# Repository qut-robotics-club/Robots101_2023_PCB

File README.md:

# ROBOTS101_2023

Goal:
To create a easy funtional Pi hat for the ROBOTS101 program.

This pi hat will:
- Label all pins & connections clearly.
- Have breakout headers to reduce confusion and reduce dangerous connections
- Regulate battery voltage & power the Pi safely 
- Provide a direct and clear power switch
- (Optional) Expand GPIO for future projects 
- Clean and streamline robot construction.
- Have an easy design for future PCB workshop to work on

ROBOTS101 WIKI LINK: https://goofy-slicer-49c.notion.site/ROBOTS101-Wiki-223888f84ce34d78a62f8b15874e6fb9

## Key Features
1. Battery Connector
    - XT30 PCB Mount
2. Power Regulation 
    - 5.1V Regulation
        - Limit to 2.5A
        - Needs filtering capacitors
        - Regulators can be bought from store
    - 3.3V Regulation? (unsure if necessary)
3. Reverse Polarity 
    - P-MOSFET
4. User Feedback
    - Buttons
    - LEDS
5. Expansion 
    - I2C address lanes - breakout into multiple connectors
6. Breakouts
    - Motor control board
    - Single Gripper Servo or two??
    - Ultrasonic Sensor
    - Adafruit Mini PiTFT support

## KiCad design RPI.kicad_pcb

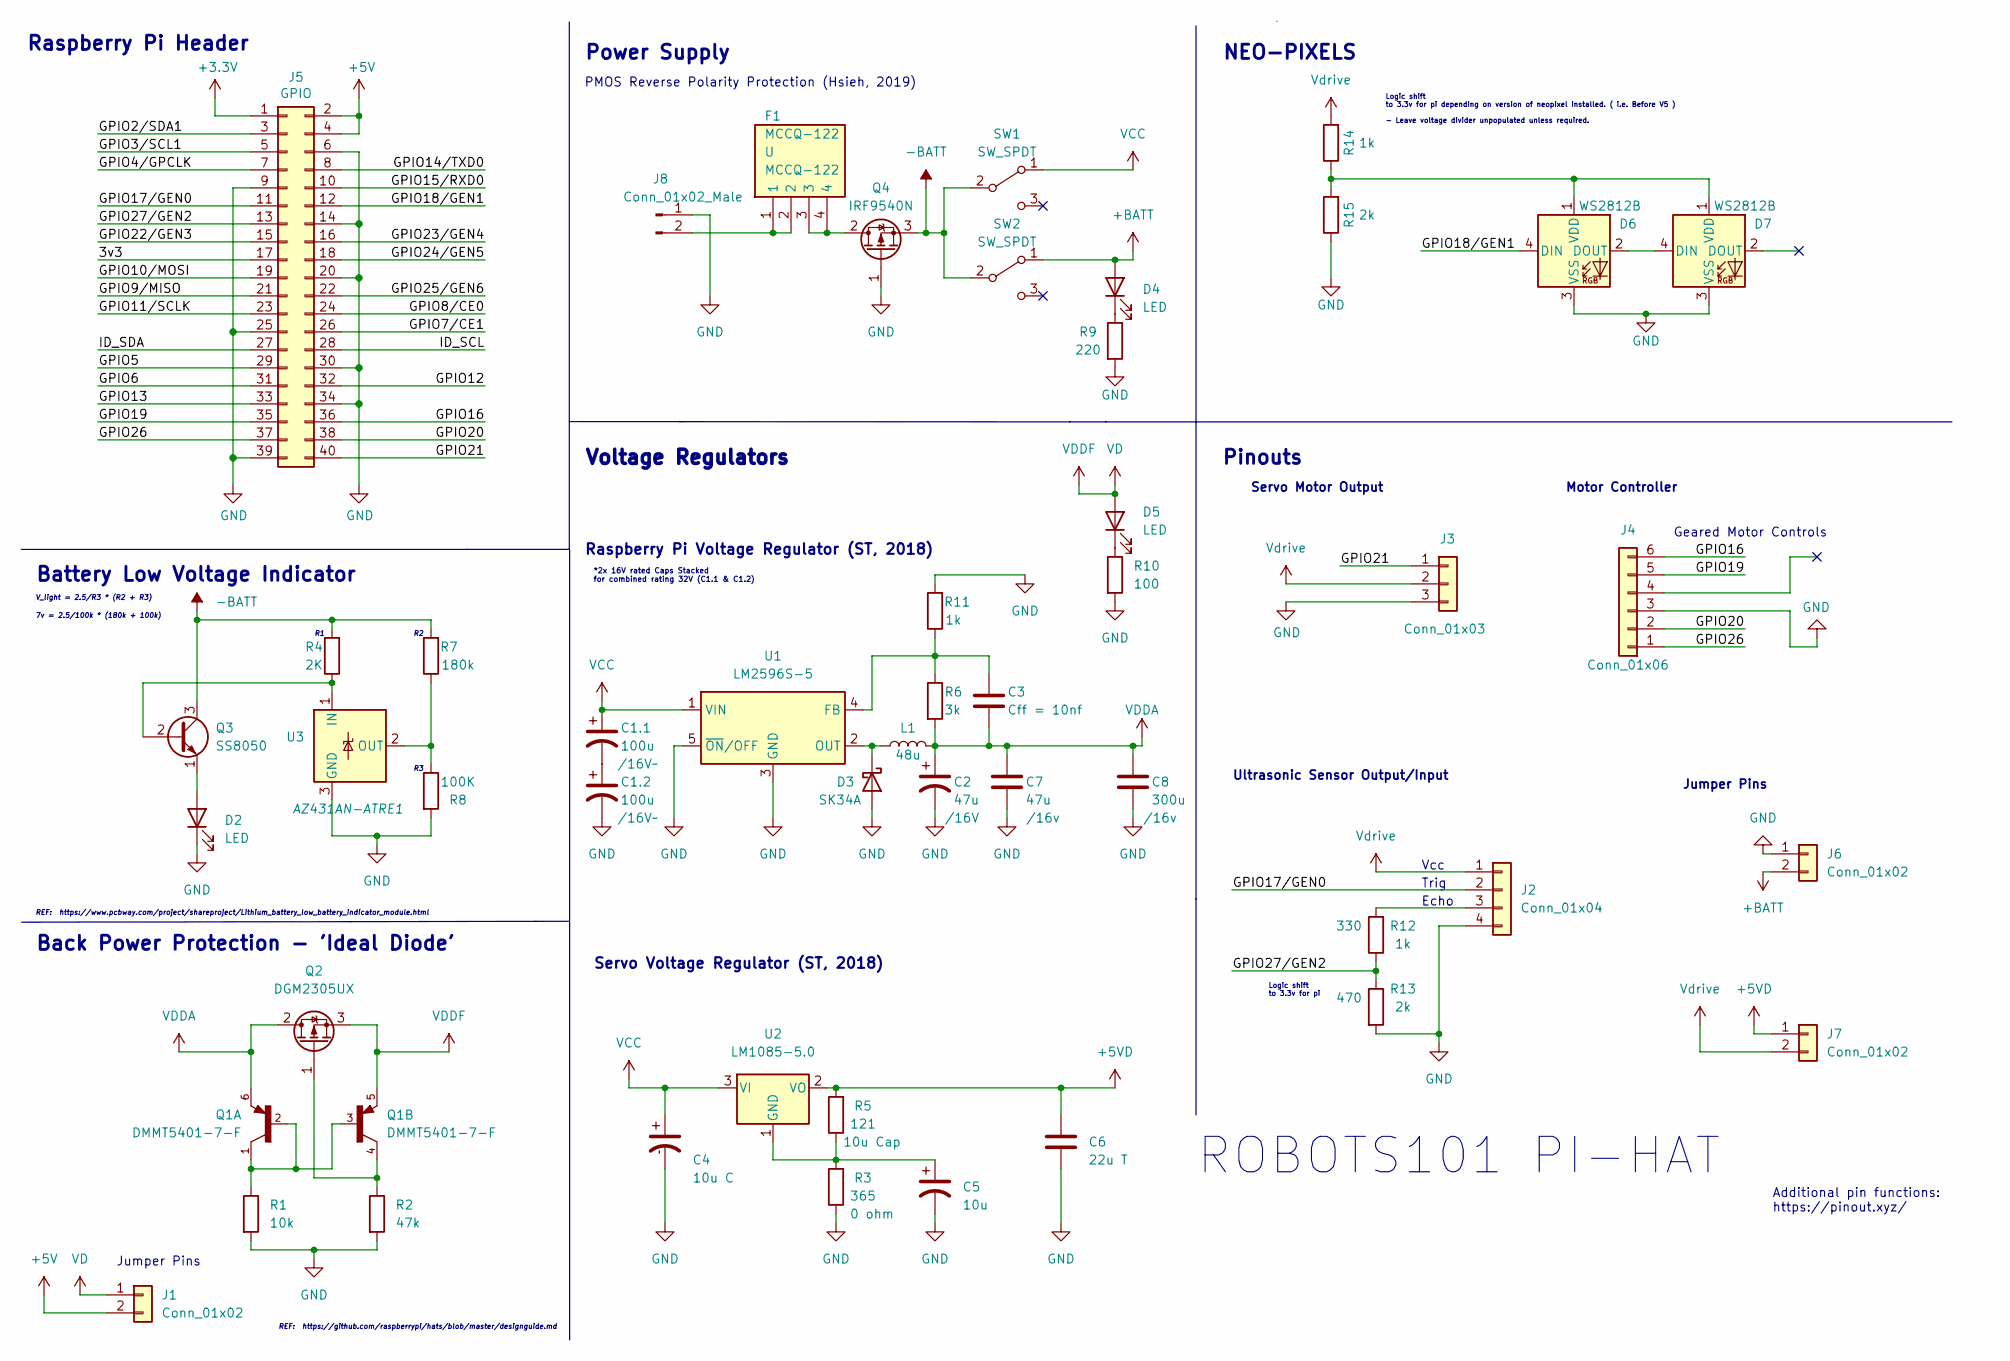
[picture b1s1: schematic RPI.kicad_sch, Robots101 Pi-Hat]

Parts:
C1.1, C1.2: 100u; C_1210_3225Metric_Pad1.33x2.70mm_HandSolder; Voltage /16V~
C2: 47u; C_0805_2012Metric_Pad1.18x1.45mm_HandSolder; Voltage /16V
C3: Cff = 10nf; C_0805_2012Metric_Pad1.18x1.45mm_HandSolder
C4: 10u C; C_0805_2012Metric_Pad1.18x1.45mm_HandSolder
C5: 10u; C_0805_2012Metric_Pad1.18x1.45mm_HandSolder
C6: 22u T; C_0805_2012Metric_Pad1.18x1.45mm_HandSolder
C7: 47u; C_0805_2012Metric_Pad1.18x1.45mm_HandSolder; Voltage /16v
C8: 300u; CP_Radial_D5.0mm_P2.50mm; Voltage /16v
D2, D4, D5: LED; D_0805_2012Metric_Pad1.15x1.40mm_HandSolder
D3: SK34A; D_SMA_Handsoldering
D6, D7: WS2812B; LED_WS2812B_PLCC4_5.0x5.0mm_P3.2mm
F1: MCCQ-122; MCCQ122; Manufacturer_Part_Number MCCQ-122
J1, J7: Conn_01x02; PinSocket_1x02_P2.54mm_Vertical
J2: Conn_01x04; PinSocket_1x04_P2.54mm_Vertical
J3: Conn_01x03; PinSocket_1x03_P2.54mm_Vertical
J4: Conn_01x06; PinSocket_1x06_P2.54mm_Vertical
J5: GPIO; PinSocket_2x20_P2.54mm_Vertical
J6: Conn_01x02; TE_282836-2
J8: Conn_01x02_Male; AMASS_XT30PW-M_1x02_P2.50mm_Horizontal
L1: 48u; L_Bourns_SRR1260
Q1: DMMT5401-7-F; SOT-23-6_Handsoldering; PARTREV 8
Q2: DGM2305UX; SOT-23
Q3: SS8050; SOT-23-3
Q4: IRF9540N; TO-220-3_Vertical
R1: 10k; R_0805_2012Metric_Pad1.20x1.40mm_HandSolder
R2: 47k; R_0805_2012Metric_Pad1.20x1.40mm_HandSolder
R3: 365; R_0805_2012Metric_Pad1.20x1.40mm_HandSolder
R4: 2K; R_0805_2012Metric_Pad1.20x1.40mm_HandSolder
R5: 121; R_0805_2012Metric_Pad1.20x1.40mm_HandSolder
R6: 3k; R_0805_2012Metric_Pad1.20x1.40mm_HandSolder
R7: 180k; R_0805_2012Metric_Pad1.20x1.40mm_HandSolder
R8: 100K; R_0805_2012Metric_Pad1.20x1.40mm_HandSolder
R9: 220; R_0805_2012Metric_Pad1.20x1.40mm_HandSolder
R10: 100; R_0805_2012Metric_Pad1.20x1.40mm_HandSolder
R11, R12, R14: 1k; R_0805_2012Metric_Pad1.20x1.40mm_HandSolder
R13, R15: 2k; R_0805_2012Metric_Pad1.20x1.40mm_HandSolder
SW1, SW2: SW_SPDT; Switch_SPDT_Jaycar
U1: LM2596S-5; TO-263-5_TabPin3
U2: LM1085-5.0; TO-220-3_Vertical
U3: AZ431AN-ATRE1; SOT-23-3

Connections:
+3V3: J5.1
+5V: J1.2, J5.2, J5.4
+5VD: C6.1, J7.1, R5.2, U2.2 (VO)
+BATT: D4.2 (A), J6.2, SW2.1 (A)
-BATT: Q3.3 (C), Q4.3 (S), R4.2, R7.2, SW1.2 (B), SW2.2 (B)
/3v3: J5.17
/GPIO2/SDA1: J5.3
/GPIO3/SCL1: J5.5
/GPIO4/GPCLK: J5.7
/GPIO5: J5.29
/GPIO6: J5.31
/GPIO7/CE1: J5.26
/GPIO8/CE0: J5.24
/GPIO9/MISO: J5.21
/GPIO10/MOSI: J5.19
/GPIO11/SCLK: J5.23
/GPIO12: J5.32
/GPIO13: J5.33
/GPIO14/TXD0: J5.8
/GPIO15/RXD0: J5.10
/GPIO16: J4.6, J5.36
/GPIO17/GEN0: J2.2, J5.11
/GPIO18/GEN1: D6.4 (DIN), J5.12
/GPIO19: J4.5, J5.35
/GPIO20: J4.2, J5.38
/GPIO21: J3.1, J5.40
/GPIO22/GEN3: J5.15
/GPIO23/GEN4: J5.16
/GPIO24/GEN5: J5.18
/GPIO25/GEN6: J5.22
/GPIO26: J4.1, J5.37
/GPIO27/GEN2: J5.13, R12.1, R13.1
/ID_SCL: J5.28
/ID_SDA: J5.27
GND: C1.2.2, C2.2, C4.2, C5.2, C6.2, C7.2, C8.2, D2.1 (K), D3.2 (A), D6.3 (VSS), D7.3 (VSS), J2.4, J3.3, J4.3, J5.6, J5.9, J5.14, J5.20, J5.25, J5.30, J5.34, J5.39, J6.1, J8.1, Q4.1 (G), R1.2, R2.2, R3.1, R8.2, R9.2, R10.2, R11.2, R13.2, R15.1, U1.3 (GND), U1.5 (~ON/OFF), U3.3 (GND)
unnamed: C1.1.2, C1.2.1
unnamed: C3.1, R6.1, R11.1, U1.4 (FB)
unnamed: C5.1, R3.2, R5.1, U2.1 (GND)
unnamed: D2.2 (A), Q3.1 (E)
unnamed: D3.1 (K), L1.1, U1.2 (OUT)
unnamed: D4.1 (K), R9.1
unnamed: D5.1 (K), R10.1
unnamed: D6.1 (VDD), D7.1 (VDD), R14.1, R15.2
unnamed: D6.2 (DOUT), D7.4 (DIN)
unnamed: F1.1, F1.2, J8.2
unnamed: F1.3, F1.4, Q4.2 (D)
unnamed: J2.3, R12.2
unnamed: Q1.1, Q1.2, Q1.3, R1.1
unnamed: Q1.4, Q2.1 (G), R2.1
unnamed: Q3.2 (B), R4.1, U3.1 (IN)
unnamed: R7.1, R8.1, U3.2 (OUT)
VCC: C1.1.1, C4.1, SW1.1 (A), U1.1 (VIN), U2.3 (VI)
VD: D5.2 (A), J1.1, Q1.5, Q2.3 (S)
VDDA: C2.1, C3.2, C7.1, C8.1, L1.2, Q1.6, Q2.2 (D), R6.2
Vdrive: J2.1, J3.2, J7.2, R14.2

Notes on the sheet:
REF: https://github.com/raspberrypi/hats/blob/master/designguide.md
ROBOTS101 PI-HAT
Logic shift to 3.3v for pi
Battery Low Voltage Indicator
Raspberry Pi Header
Vcc
Jumper Pins
Pinouts
Additional pin functions: https://pinout.xyz/
Servo Motor Output
REF: https://www.pcbway.com/project/shareproject/Lithium_battery_low_battery_indicator_module.html
PMOS Reverse Polarity Protection (Hsieh, 2019)
V_light = 2.5/R3 * (R2 + R3)
*2x 16V rated Caps Stacked for combined rating 32V (C1.1 & C1.2)
Servo Voltage Regulator (ST, 2018)
Echo
Power Supply
Logic shift to 3.3v for pi depending on version of neopixel installed. ( i.e. Before V5 ) - Leave voltage divider unpopulated unless required.
Trig
Ultrasonic Sensor Output/Input
Back Power Protection - 'Ideal Diode'
Motor Controller
7v = 2.5/100k * (180k + 100k)
Raspberry Pi Voltage Regulator (ST, 2018)
Voltage Regulators
NEO-PIXELS
Geared Motor Controls

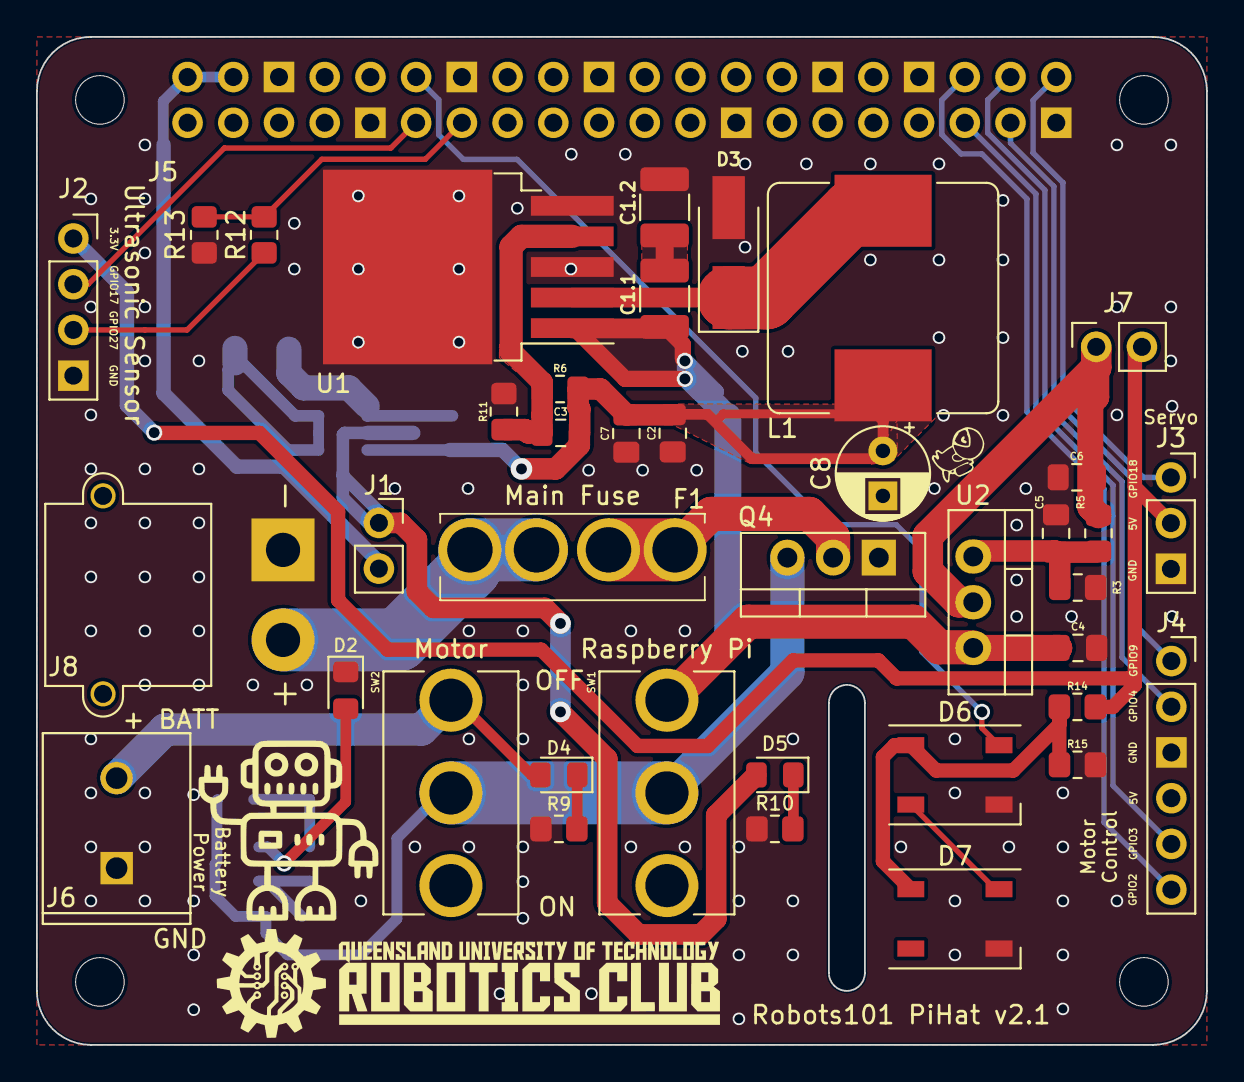
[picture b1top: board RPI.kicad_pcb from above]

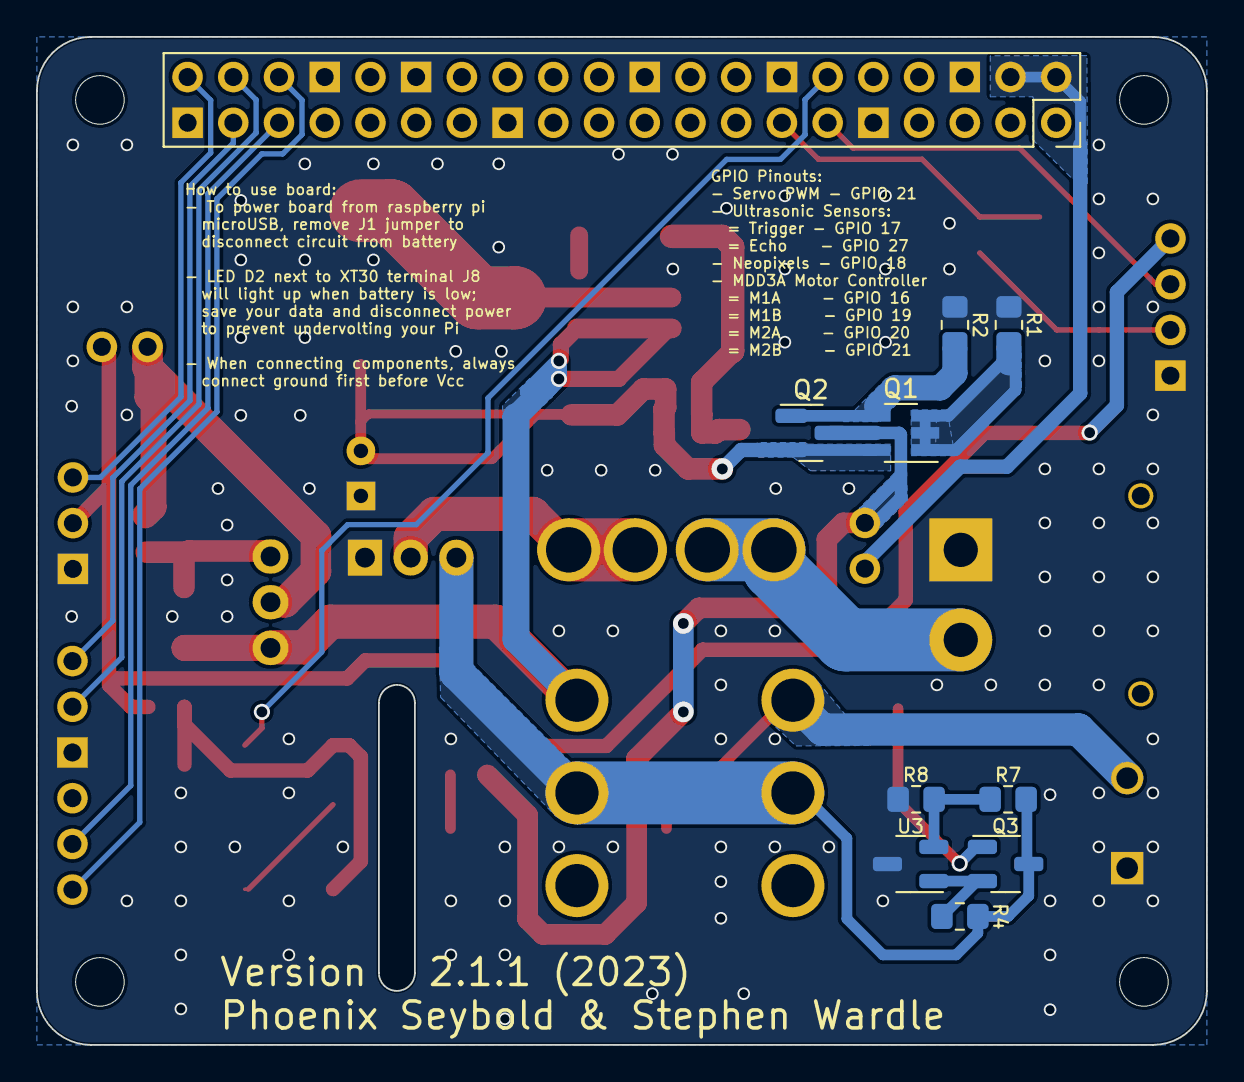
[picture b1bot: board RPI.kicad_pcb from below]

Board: 2 copper layers, 65.0 x 56.0 mm, 56 parts (10 on the bottom side), 33 nets.

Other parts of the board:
G: LOGO
G#2: LOGO
MH1, MH2, MH3, MH4: MountingHole_2.7mm_M2.5
ROBOTS101: LOGO

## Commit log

2023-02-13 adding stevens 1st PCB draft
2023-02-13 added folder structure | UNFORTUNATLY REQUIRED DUMMY TEXT FILES
2023-02-13 Update README.md
    feature overview
2023-02-16 Updated MOSFET and Vreg to be store-accessible
2023-02-16 Spelling error correction and updates of README.md
2023-02-16 Updated Adafruit Pinouts & Pi Pinouts
2023-02-17 Adding part numbers + updated footprint for a pin
2023-03-01 Updated GPIO numbers correctly on pi
2023-03-02 Updates made to reflect actual correct pin labels
2023-03-02 Updated for motor driver, UV sensor, & servo pins
2023-03-02 Schematic Completed
2023-03-03 Added diode protection and switches
2023-03-03 Revisions made?
2023-03-03 Small update
2023-03-05 Removed EEPROM, Added back power protection
2023-03-15 Process to update headers for SMDs
2023-03-15 Component footprints done - only need cap & sw tbd
2023-03-19 Completed Schematic, just need to edit footprints
2023-03-27 All symbols updated
2023-03-27 Checking about footprint
2023-03-28 Official completion (Maybe add Gerald in)
2023-03-28 Student Version
2023-03-28 Revert "Student Version"
    This reverts commit 96f77fa7ec59c85fd2b51f56cc1ae2b80deb0d98.
2023-03-28 Just need to add Gerald
2023-03-28 Official Library included, needed in global lib
2023-03-31 Added Fuse
2023-03-31 Finalised for a check-up
2023-03-31 Gerber files generated?
2023-03-31 fixed up using Fab ruleset and Matt's input
2023-03-31 Added load resistor & updated footprints
2023-03-31 Further updated with more resistors
2023-03-31 Updated parallel res due to poor understanding
2023-04-01 Thickened 5V rail
2023-04-01 Changed regulator
2023-04-24 Added DMMT library
2023-04-25 V2 Ready for checking
2023-04-25 V2 update with THT copper shapes and info given
2023-07-25 V2 Overhaul with new circuits and GPIO routes
2023-07-25 Complete file replacement to fix corrupted version
2023-08-01 Added via stitching and titles
2023-08-01 Fixed trace thickness to 0.3 for R12 & R13
2023-08-01 Thickened traces for Vcc
2023-08-06 Updated Schematic & finalised PCB design
    - Schematic more readable
    - Finalised silkscreen
    - Generate Gerber
    - Cleaned Folder structure
    - Added missing 3D models
2023-08-06 Slight placement adjustment of schematic
2023-08-06 added ref to Ideal diode
2023-08-06 Minor
2023-08-06 Switch input cap to 1210 package for 100uf @16v
2023-08-06 minor Vias edits for text readability
2023-08-06 Changed nets to more approachable labels
2023-08-06 minor readability tweaks
2023-08-06 Updated drawing info
2023-08-06 fixed DRC Issues
2023-08-06 minor fixes
2023-08-29 v2.1 Fixed Battery switch Direction
    Pushed after 2nd PCB order
